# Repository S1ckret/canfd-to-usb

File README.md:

View this project on [CADLAB.io](https://cadlab.io/project/22559). 

# canfd-to-usb

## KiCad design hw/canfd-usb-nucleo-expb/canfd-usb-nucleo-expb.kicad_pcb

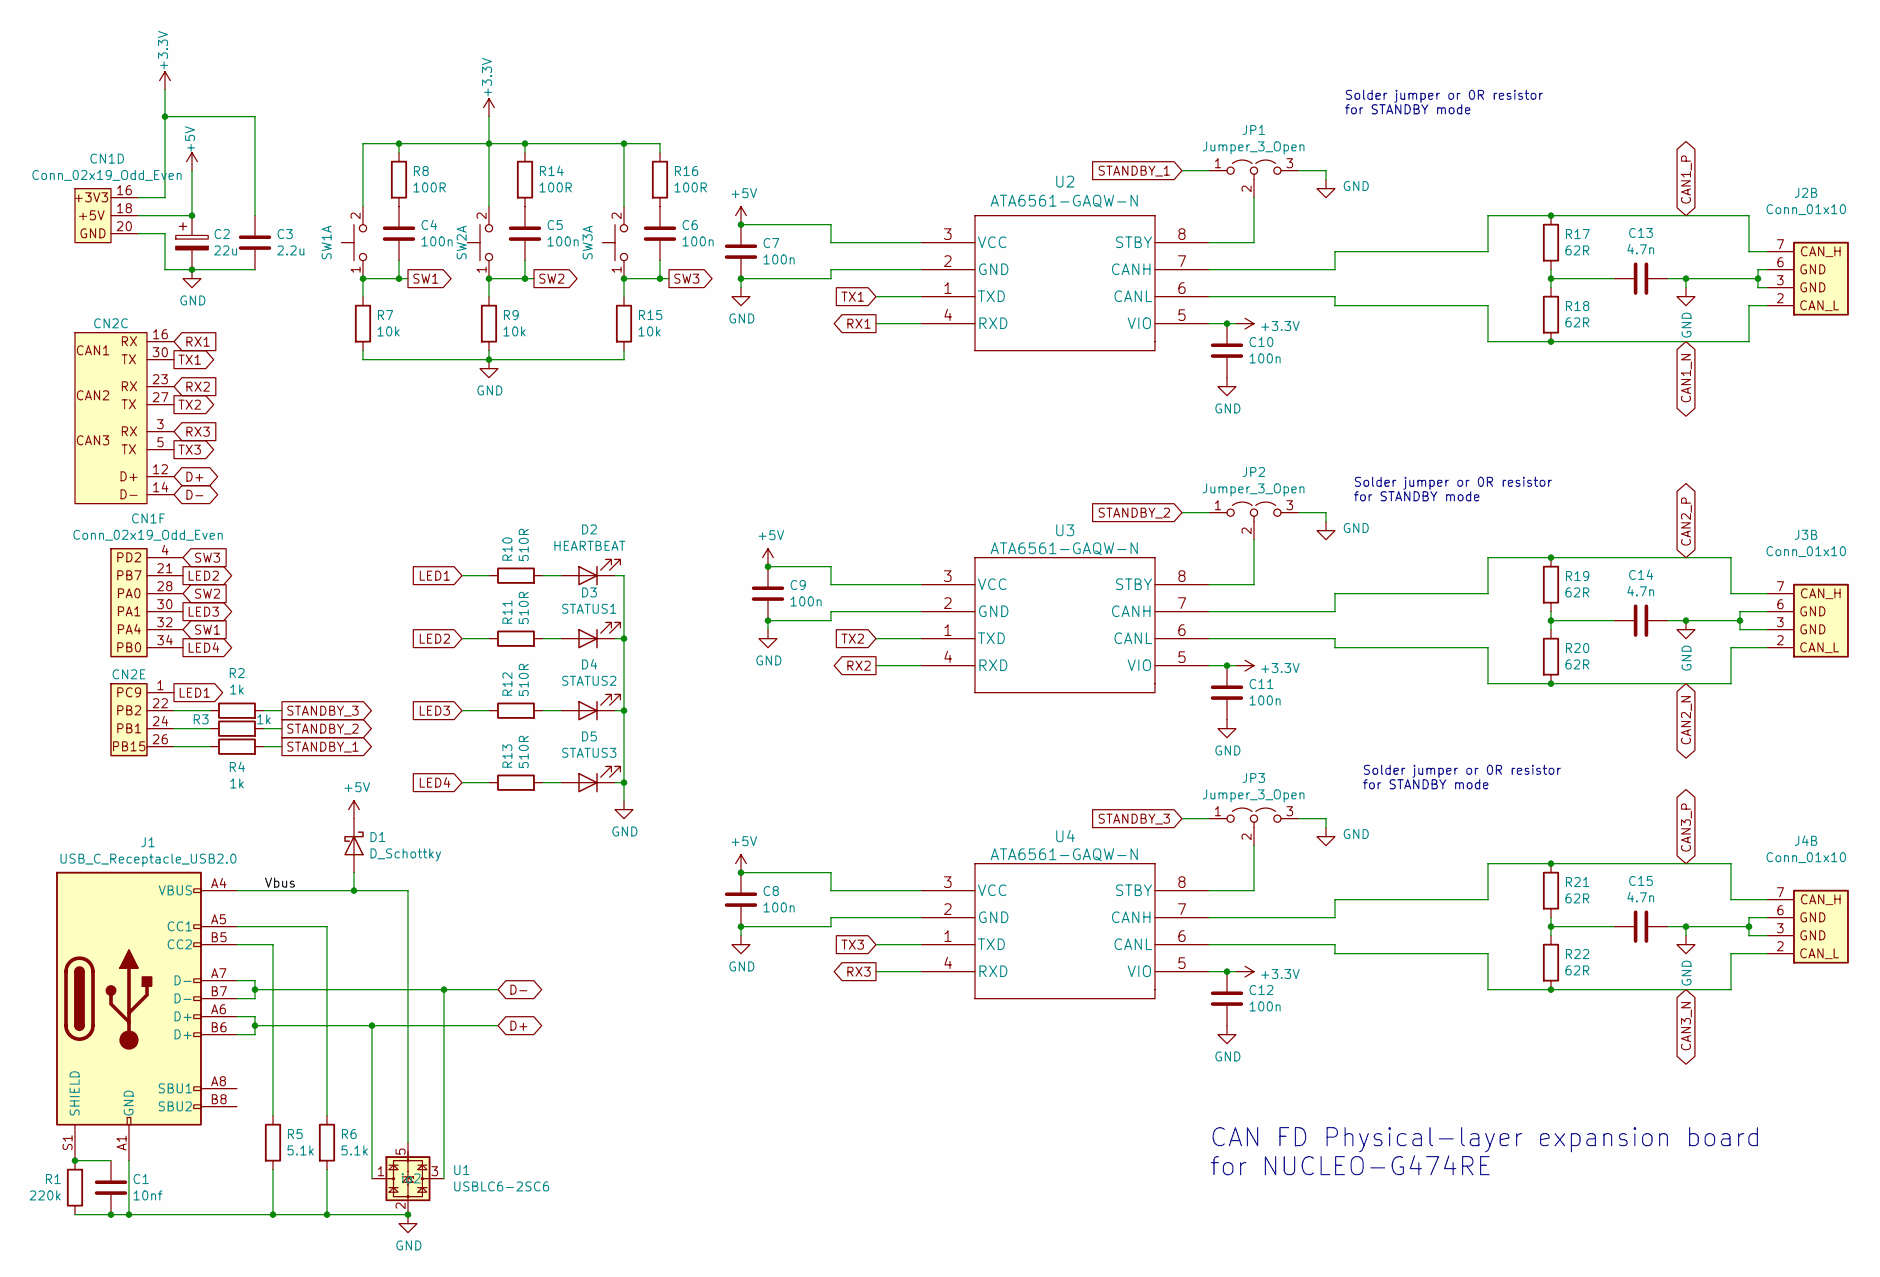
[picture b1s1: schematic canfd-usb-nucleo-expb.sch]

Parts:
C1: 10nf; C_0805_HandSoldering
C2: 22u; C_1206_3216Metric
C3: 2.2u; C_0805_HandSoldering
C4, C5, C6, C7, C8, C9, C10, C11, C12: 100n; C_0805_HandSoldering
C13, C14, C15: 4.7n; C_0805_HandSoldering
CN1: Conn_02x19_Odd_Even; Pin_Header_Straight_2x19_Pitch2.54mm
CN2: CONN; Pin_Header_Straight_2x19_Pitch2.54mm
D1: D_Schottky; D_SOD-123
D2: HEARTBEAT; LED_D3.0mm
D3: STATUS1; LED_D3.0mm
D4: STATUS2; LED_D3.0mm
D5: STATUS3; LED_D3.0mm
J1: USB_C_Receptacle_USB2.0; L-KLS1-TIPEC-B
J2, J3, J4: Conn_01x10; IDC-Header_2x05_P2.54mm_Vertical
JP1, JP2, JP3: Jumper_3_Open; SolderJumper-3_P1.3mm_Open_RoundedPad1.0x1.5mm
R1: 220k; R_0805_HandSoldering
R2, R3, R4: 1k; R_0805_HandSoldering
R5, R6: 5.1k; R_0805_HandSoldering
R7, R9, R15: 10k; R_0805_HandSoldering
R8, R14, R16: 100R; R_0805_HandSoldering
R10, R11, R12, R13: 510R; R_0805_HandSoldering
R17, R18, R19, R20, R21, R22: 62R; R_0805_HandSoldering
SW1, SW2, SW3: SW_Push_Dual_x2; SW_PUSH_6mm
U1: USBLC6-2SC6; SOT-23-6_Handsoldering
U2, U3, U4: ATA6561-GAQW-N; SOIC-8_3.9x4.9mm_Pitch1.27mm

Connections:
+3V3: C3.1, C10.1, C11.1, C12.1, CN1.16, R8.1, R14.1, R16.1, SW1.2 (D), SW2.2 (D), SW3.2 (D), U2.5 (VIO), U3.5 (VIO), U4.5 (VIO)
+5V: C2.1, C7.1, C8.1, C9.1, CN1.18, D1.1 (K), U2.3 (VCC), U3.3 (VCC), U4.3 (VCC)
/Vbus: D1.2 (A), J1.A4 (VBUS), J1.A9 (VBUS), J1.B4 (VBUS), J1.B9 (VBUS), U1.5
CAN1_N: J2.2, R18.2, U2.6 (CANL)
CAN1_P: J2.7, R17.1, U2.7 (CANH)
CAN2_N: J3.2, R20.2, U3.6 (CANL)
CAN2_P: J3.7, R19.1, U3.7 (CANH)
CAN3_N: J4.2, R22.2, U4.6 (CANL)
CAN3_P: J4.7, R21.1, U4.7 (CANH)
D+: CN2.12, J1.A6 (D+), J1.B6 (D+), U1.1, U1.6 (io1)
D-: CN2.14, J1.A7 (D-), J1.B7 (D-), U1.3 (io2), U1.4 (io2)
GND: C1.2, C2.2, C3.2, C7.2, C8.2, C9.2, C10.2, C11.2, C12.2, C13.2, C14.2, C15.2, CN1.20, D2.1 (K), D3.1 (K), D4.1 (K), D5.1 (K), J1.A1 (GND), J1.A12 (GND), J1.B1 (GND), J1.B12 (GND), J2.3, J2.6, J3.3, J3.6, J4.3, J4.6, JP1.3 (B), JP2.3 (B), JP3.3 (B), R1.1, R5.2, R6.2, R7.2, R9.2, R15.2, U1.2, U2.2 (GND), U3.2 (GND), U4.2 (GND)
LED1: CN2.1, R10.1
LED2: CN1.21, R11.1
LED3: CN1.30, R12.1
LED4: CN1.34, R13.1
unnamed: C1.1, J1.S1 (SHIELD), R1.2
unnamed: C4.1, R8.2
unnamed: C5.1, R14.2
unnamed: C6.1, R16.2
unnamed: C13.1, R17.2, R18.1
unnamed: C14.1, R19.2, R20.1
unnamed: C15.1, R21.2, R22.1
unnamed: CN2.22, R2.1
unnamed: CN2.24, R3.1
unnamed: CN2.26, R4.1
unnamed: D2.2 (A), R10.2
unnamed: D3.2 (A), R11.2
unnamed: D4.2 (A), R12.2
unnamed: D5.2 (A), R13.2
unnamed: J1.A5 (CC1), R6.1
unnamed: J1.B5 (CC2), R5.1
unnamed: JP1.2 (C), U2.8 (STBY)
unnamed: JP2.2 (C), U3.8 (STBY)
unnamed: JP3.2 (C), U4.8 (STBY)
RX1: CN2.16, U2.4 (RXD)
RX2: CN2.23, U3.4 (RXD)
RX3: CN2.3, U4.4 (RXD)
STANDBY_1: JP1.1 (A), R4.2
STANDBY_2: JP2.1 (A), R3.2
STANDBY_3: JP3.1 (A), R2.2
SW1: C4.2, CN1.32, R7.1, SW1.1 (C)
SW2: C5.2, CN1.28, R9.1, SW2.1 (C)
SW3: C6.2, CN1.4 (PD2), R15.1, SW3.1 (C)
TX1: CN2.30, U2.1 (TXD)
TX2: CN2.27, U3.1 (TXD)
TX3: CN2.5, U4.1 (TXD)

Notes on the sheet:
CAN FD Physical-layer expansion board for NUCLEO-G474RE
Solder jumper or 0R resistor for STANDBY mode

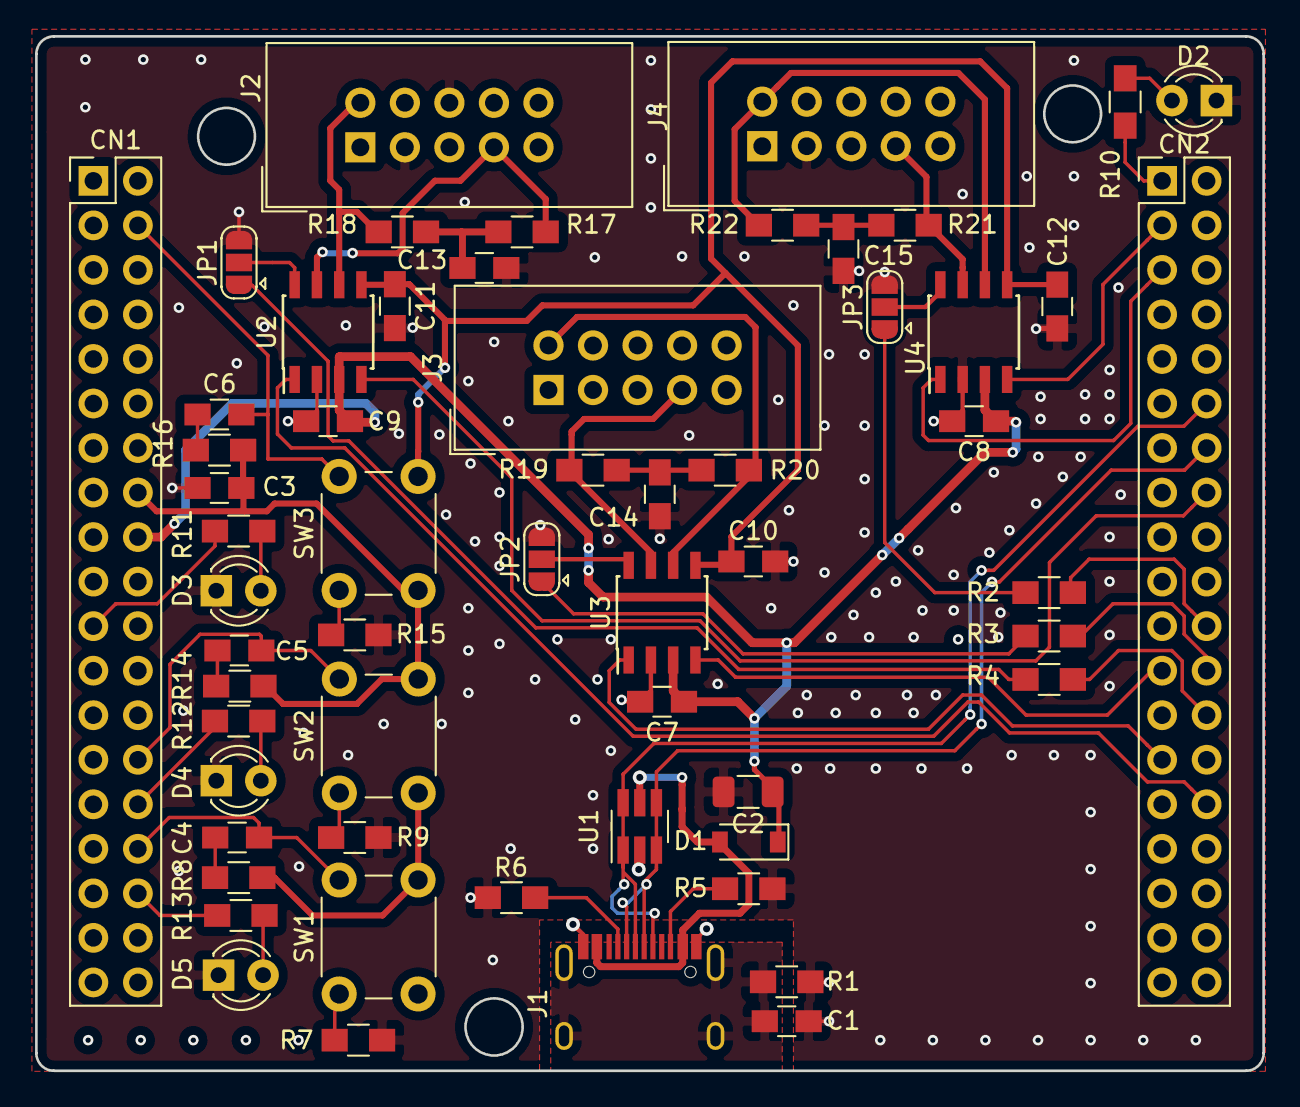
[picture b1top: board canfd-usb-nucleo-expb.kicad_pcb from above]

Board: 2 copper layers, 70.0 x 59.0 mm, 58 parts (0 on the bottom side), 47 nets.

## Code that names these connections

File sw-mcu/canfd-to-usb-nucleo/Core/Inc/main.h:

/* USER CODE BEGIN Header */
/**
  ******************************************************************************
  * @file           : main.h
  * @brief          : Header for main.c file.
  *                   This file contains the common defines of the application.
  ******************************************************************************
  * @attention
  *
  * <h2><center>&copy; Copyright (c) 2020 STMicroelectronics.
  * All rights reserved.</center></h2>
  *
  * This software component is licensed by ST under BSD 3-Clause license,
  * the "License"; You may not use this file except in compliance with the
  * License. You may obtain a copy of the License at:
  *                        opensource.org/licenses/BSD-3-Clause
  *
  ******************************************************************************
  */
/* USER CODE END Header */

/* Define to prevent recursive inclusion -------------------------------------*/
#ifndef __MAIN_H
#define __MAIN_H

#ifdef __cplusplus
extern "C" {
#endif

/* Includes ------------------------------------------------------------------*/
#include "stm32g4xx_hal.h"
#include "stm32g4xx_ll_pwr.h"

/* Private includes ----------------------------------------------------------*/
/* USER CODE BEGIN Includes */

/* USER CODE END Includes */

/* Exported types ------------------------------------------------------------*/
/* USER CODE BEGIN ET */

/* USER CODE END ET */

/* Exported constants --------------------------------------------------------*/
/* USER CODE BEGIN EC */

/* USER CODE END EC */

/* Exported macro ------------------------------------------------------------*/
/* USER CODE BEGIN EM */

/* USER CODE END EM */

/* Exported functions prototypes ---------------------------------------------*/
void Error_Handler(void);

/* USER CODE BEGIN EFP */

/* USER CODE END EFP */

/* Private defines -----------------------------------------------------------*/
#define SW2_Pin GPIO_PIN_0
#define SW2_GPIO_Port GPIOA
#define LED3_Pin GPIO_PIN_1
#define LED3_GPIO_Port GPIOA
#define SW1_Pin GPIO_PIN_4
#define SW1_GPIO_Port GPIOA
#define LED4_Pin GPIO_PIN_0
#define LED4_GPIO_Port GPIOB
#define STANDBY_2_Pin GPIO_PIN_1
#define STANDBY_2_GPIO_Port GPIOB
#define STANDBY_3_Pin GPIO_PIN_2
#define STANDBY_3_GPIO_Port GPIOB
#define LED_HEARTBEAT_Pin GPIO_PIN_11
#define LED_HEARTBEAT_GPIO_Port GPIOB
#define STANDBY_1_Pin GPIO_PIN_15
#define STANDBY_1_GPIO_Port GPIOB
#define LED1_Pin GPIO_PIN_9
#define LED1_GPIO_Port GPIOC
#define SW3_Pin GPIO_PIN_2
#define SW3_GPIO_Port GPIOD
#define LED2_Pin GPIO_PIN_7
#define LED2_GPIO_Port GPIOB
/* USER CODE BEGIN Private defines */

/* USER CODE END Private defines */

#ifdef __cplusplus
}
#endif

#endif /* __MAIN_H */

/************************ (C) COPYRIGHT STMicroelectronics *****END OF FILE****/

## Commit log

2020-03-02 Backlink to CADLAB.io has been added.
2020-03-24 Project configuration: Generate empty project in Cube
    - Clear pinout
2020-03-24 Project configuration: Add led heartbeat pinout
    - pin PB11
2020-03-24 Project configuration: Add serial wire debug
2020-03-24 Project configuration: Add FreeRTOS
    - Timebase source is changed to TIM2
    - heartbeatTask is created
2020-03-24 Feature: Add heartbeat
2020-03-31 Project configuration: Squash heartbeatTask into defaultTask
2020-03-31 Fix: Move heartbeatTask into separate file.
2020-04-03 Project configuration: Add .gitignore
2020-04-03 Project configuration: Add pin layout
    CAN modules:
    - CAN_1_Tx - PB9
    - CAN_1_Rx - PB8
    - CAN_2_Tx - PB13
    - CAN_2_Rx - PB12
    - CAN_3_Tx - PB4
2020-04-03 Project configuration: Add interupts for CAN
    - Set up interupts for FIFO 0, 1
2020-04-03 Project configuration: Add USB middleware, generate code
2020-04-04 Project configuration: set CAN1 internal loopback mode
2020-04-05 Feature: Add CAN transiver task, Receive from IRQ
2020-04-05 Project configuration: Modify .gitignore
2020-04-06 Feature: Add queues logic
    - Add queue from usbTask to CAN1Task
    - Add queue from CAN1Task to usbTask
    - Send to queues from interupts like (Rx0Callback, CDC_Receive)
    - usbTask sends received data from CANs to user PC
    - CAN1Task sends received data from USB to device
2020-04-13 LPUART: Generate pins
    - Add LPUART for testing instead of USB.
2020-04-13 LPUART: Add task and callback
    - Task sends data to PC
    - Callback receives data from PC
2020-04-16 FDCAN: Add flexible task creation
2020-04-16 FDCAN Usage: Fix variables declarations
2020-04-16 USB UART: Rewrite modules to new API
2020-04-16 FDCAN: Add receive callback
2020-04-16 USB: Add receive callback
    - Heap size increased to startup the USB Middleware
2020-04-16 Refactoring: Change queue names to FreeRTOS code style
2020-04-16 Task Creation: Fix order
    - You have to create tasks after queues
2020-04-17 FDCAN: Add ability to send to different modules
    - Add config file
2020-04-17 FDCAN: Add file for callbacks
2020-04-23 Project configuraution: Reassign pins to latest PCV version
2020-04-24 FDCAN: Add callbacks with new pins
2020-04-24 USB: Fix queues and data transmission
2020-04-24 LPUART: Remove all content
2020-04-24 USB: Add messege proccesing
2020-04-24 FDCAN: Configure all modules to Normal mode
2020-04-24 FDCAN: Set up modules for sending
    - For board that works like device (tranceiver)
2020-06-30 Configuration: Add serial wire debug
2020-06-30 Configuration: Add high speed clock
2020-06-30 Configuration: Add 3 canfd
2020-06-30 Configuration: Add usb
2020-06-30 Configuration: Add usb middleware as cdc
2020-06-30 Configuration: Add 4 leds
2020-06-30 Configuration: Add 3 standby switches
2020-06-30 Configuration: Add 3 switches as EXTI
2020-06-30 Configuration: Add FreeRTOS
2020-06-30 Configuration: Add LPUART for debug through st-link
2020-06-30 FreeRTOS: Rewrite syntax to default from cmsis_v2
2020-07-04 FreeRTOS: Add heartbeat (default) task
2020-07-04 Configuration: Add gitignore
2020-07-04 Fdcan: Add module handle
2020-07-04 FDCAN: Add Init function
2020-07-04 FDCAN: Add error handler and checker
2020-07-04 FDCAN: Add start function
2020-07-04 FDCAN: Add notification activation function
2020-07-04 FDCAN: Add simple check in init func
2020-07-04 FDCAN: Add separate file with structure definition
2020-07-04 FDCAN: Rewrite initialization
2020-07-04 Interrupts: Add fdcan and exti
2020-07-04 LPUART: Add global interrupt
2020-07-04 FreeRTOS: Move heartbeat task from main
2020-07-04 FDCAN: Activate interrupts
2020-07-04 FDCAN: Start modules
2020-07-04 FDCAN: Add set_tx_header function
2020-07-04 FDCAN: Set tx headers for 3 modules
2020-07-04 FreeRTOS: Add queues for fdcans and usb
2020-07-04 Interrupts: Test buttons via leds
2020-07-04 FDCAN: Refactor user pointers
    Put pointers into array for conveniency
2020-07-04 FreeRTOS: Increase heap memory to 8192
2020-07-04 FDCAN: Add utility functions
    get_payload
    send_payload
2020-07-04 FreeRTOS: Add fdcan task with notification
2020-07-04 FDCAN: Test notification via buttons
2020-07-09 FreeRTOS: Rename heartbeat_task to task_heartbeat
2020-07-09 FDCAN: Fix double pointer parameter
2020-07-09 FreeRTOS: Add usb task
2020-07-09 Interrupts: Add fdcan receive callback
2020-07-09 FDCAN: Rename canfdTaskHandle to fdcanTaskHandle
2020-07-09 FDCAN: Add utility id map functions
    User can enter his own id for fdcan module. So I add those functions
    to get access to corresponding modules.
2020-07-09 USB: Add receive callback logic
2020-07-13 Circular buffer: Remove dynamical allocation
2020-07-13 Add circular buffer
    I have added circular buffer for usb receiving. We need to form
    messages with a certain length (Ex: 64/32/8 bytes).
    Buffer have a callback. When usb will receive data circular buffer
    fills up and emmits callbacks.
2020-07-13 Circular buffer: Add callback and init
2020-07-27 Configuration: Delete .mxproject
    I have deleted .mxproject to avoid misleading which project to load.
    In addition .mxproject is old.
2020-07-29 FDCAN: Add filter configuration
2020-07-29 FDCAN-debug: Add message sending on buttons
